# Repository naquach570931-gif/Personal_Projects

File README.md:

* Objective: Design Power electronics: Buck Converter, Boost Converter, and SEPIC Converter

* Determine set parameters: Vin, Vout, Ioutmax, D to calculate inductance value, capacitance values, and ripples.

* Compared theortical values to measurements via LTspice simulation.

* Designed PCB from schematic layout to pcb layout, through the process of incorporating manufacturing part numbers and rooting process.

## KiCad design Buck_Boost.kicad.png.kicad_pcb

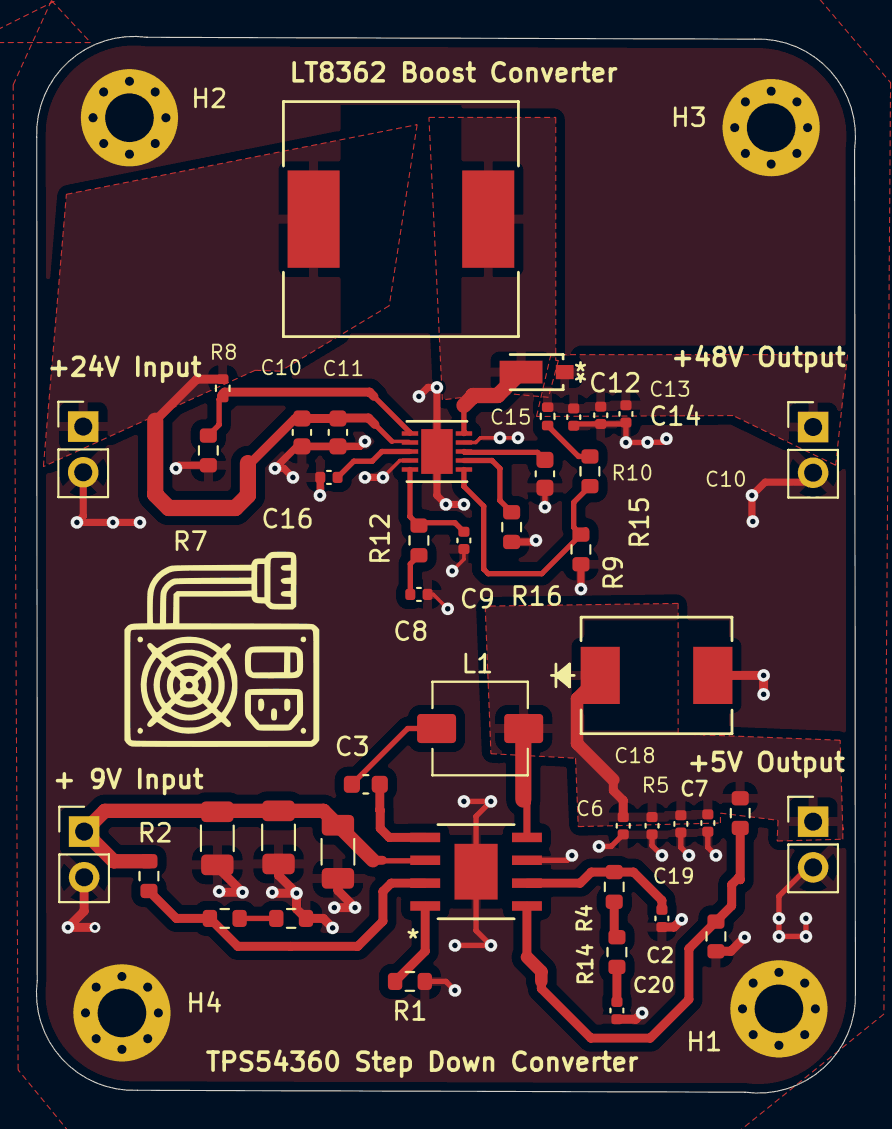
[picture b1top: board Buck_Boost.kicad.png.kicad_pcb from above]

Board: 2 copper layers, 45.5 x 58.7 mm, 48 parts (0 on the bottom side), 23 nets.

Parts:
C2: 48p; C_0402_1005Metric
C3: 0.1u; C_0603_1608Metric
C4, C5, C17: 10u; C_1206_3216Metric
C6, C7, C12, C13, C14, C18, C19: 10u; C_0402_1005Metric
C8: 100p; C_0402_1005Metric
C9: 3p; C_0402_1005Metric
C10, C11: 4.7u; C_0603_1608Metric
C15: 10n; C_0603_1608Metric
C16: 1u; C_0402_1005Metric
C20: 4n; C_0402_1005Metric
D1: D; SMC_DIO
D2: D; SDO_POWERDI123_DIO
H1, H2, H3, H4: MountingHole_Pad; MountingHole_2.7mm_M2.5_Pad_Via
J1, J3: Conn_01x02_Socket; PinHeader_1x02_P2.54mm_Vertical
J2, J4: Conn_01x02_Pin; PinHeader_1x02_P2.54mm_Vertical
L1: 4.7u; INDM5752X300N
L2: 10u; IND_BOURNS_SRR1240
R1: 102k; R_0603_1608Metric
R2: 300k; R_0603_1608Metric
R3, R13: 22k; R_0603_1608Metric
R4: 40k; R_0603_1608Metric
R5: 1Meg; R_0603_1608Metric
R6: 200k; R_0603_1608Metric
R7: 3.79k; R_0603_1608Metric
R8: 50k; R_0402_1005Metric
R9: 25k; R_0603_1608Metric
R10: 715k; R_0402_1005Metric
R12: 5k; R_0603_1608Metric
R14: 4k; R_0603_1608Metric
R15: 10k; R_0603_1608Metric
R16: 45.3k; R_0603_1608Metric
U1: TPS54360DDAR; DDA8_3P1X2P4_TEX-M
U2: LT8362EDD-TRPBF; 05-08-1699_ADI-M

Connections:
+5V: C6.2, C7.2, C18.2, C19.2, D1.1 (K), J1.1, L1.2, R5.1, U1.8 (SW)
+9V: C4.1, C5.1, C17.1, J2.1, R2.1, U1.2 (VIN)
+24V: C10.1, C11.1, J4.1, L2.1, R8.1, U2.2 (VIN)
+48V: C12.1, C13.1, C14.1, D2.1 (K), J3.1, R10.1
FB: R5.2, R6.1, U1.5 (FB)
GND: C2.2, C4.2, C5.2, C6.1, C7.1, C8.2, C9.2, C10.2, C11.2, C12.2, C13.2, C14.2, C15.2, C16.2, C17.2, C18.1, C19.1, C20.2, D1.2 (A), H1.1, H2.1, H3.1, H4.1, J1.2, J2.2, J3.2, J4.2, R1.2, R6.2, R7.2, R9.2, R13.2, R16.2, U1.7 (GND), U1.EPAD, U2.4 (BIAS), U2.9 (SYNC/MODE), U2.11 (PGND/GND)
unnamed: C3.2, L1.1
unnamed: C8.1, R12.2
unnamed: C20.1, R14.2
unnamed: D2.2 (A), L2.2, U2.10 (SW)
unnamed: R10.2, R15.1
unnamed: R3.2, R13.1
unnamed: R4.2, R14.1
unnamed: C3.1, U1.1 (BOOT)
unnamed: C2.1, R4.1, U1.6 (COMP)
unnamed: R2.2, R3.1, U1.3 (EN)
unnamed: R1.1, U1.4 (RT/CLK)
unnamed: R7.1, R8.2, U2.1 (EN/UVLO)
unnamed: R9.1, R15.2, U2.6 (FBX)
unnamed: C16.1, U2.3 (INTVCC)
unnamed: R16.1, U2.7 (RT)
unnamed: C15.1, U2.8 (SS)
unnamed: C9.1, R12.1, U2.5 (VC)

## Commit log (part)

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2026-06-22 Rename Screenshot 2026-06-20 175427.png to Measurements
2026-06-23 Revise README with project objectives and details
    Updated project objective and added details on design and measurements.
